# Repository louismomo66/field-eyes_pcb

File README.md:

# Field Eyes v2: full board schematic (KiCad 9)

Open `field_eyes_v2.kicad_pro` in KiCad 9. The whole circuit is **one flat schematic** (`field_eyes_v2.kicad_sch`): all 168 parts are on a single page, in four framed sections. The same page is in `field_eyes_v2.pdf`, and the parts list is in `field_eyes_v2_bom.csv`.

The design has 168 parts. KiCad's electrical rules check (ERC) reports 0 violations, and every net connects at least two pins.

**Status: schematic only.** There is no PCB layout yet. Nothing has been built or tested.

| Section (frame on the page) | Contents |
|---|---|
| Top of the page | Title, power tree, what changed from the old board, PCB layout notes |
| 1 Power (parts R1xx, C1xx...) | 6 V solar panel → CN3791 MPPT charger → 18650 cell with DW01A + FS8205 protection. XC6220 3.3 V regulator. AO3401A-switched +3V3_SW and +12V_SENS (MT3608 boost). Battery voltage, temperature and charge-status sensing. |
| 2 ESP32 (2xx) | ESP32-WROOM-32D. EN delay. Programming header **SV1** (the same 2 × 3 header and pin order as the old board: DTR, 3V3, TX, RX, RTS, GND) with auto-reset. OLED (**X3**) and DHT22 (**X4**) on 4-pin JST XH connectors with the old board's pinouts. 4 × M3 mounting holes. ESP32 pin map. |
| 3 Modem (3xx) | A7672S running straight from the cell, with 470 µF and the SIMCom capacitor set. PWRKEY and RESET drivers. UART level shifters. RI wake. Network LED. SIM holder with 22 Ω resistors and ESD. U.FL antenna with matching pads. Service header for modem firmware updates. |
| 4 Sensors and valve (4xx) | 2 × **MAX485ESA+T** RS485 (SMT100 on **X2**, 7-in-1 on **X1**) with automatic direction and SM712 protection. X1/X2 are 4-pin JST XH, pin 1 A, 2 B, 3 +12 V, 4 GND, as on the old board. A 78L05 (U405) makes the 5 V the MAX485 needs; dividers (3.3k/6.8k) bring its receive output down to 3.4 V for the ESP32. MX1508 driver for the latching valve (the chip from your mini-L298N module). |

The first version had four separate sheets behind placeholder boxes. Those files, and the board file as it was, are kept in `old_hierarchical/`; the circuit is identical (every net connects the same pins) and the board was relinked to the flat schematic.

`field_eyes.kicad_sym` holds custom symbols for the CN3791, FS8205, A7672S, SIM holder and SMF05C. The A7672S and SIM-holder footprints in `field_eyes.pretty` are copied from your current board, so they match what was already fabricated.

## Main decisions

- **Supply:** one Li-ion cell (VSYS 3.0–4.2 V).
  - The A7672S runs straight from it, as in SIMCom's reference design. That removes the MP2338 buck, the LM1117 and the D6/D7 diode drop.
  - Solar MPPT charging and cell protection are on the board.
  - Details and the battery-life estimate are in `../power_v2/README.md`. That earlier power-only project is now part of this one.
- **Everything that isn't needed is off by default.** The modem stays off until GPIO26 presses its power key. Sensors, RS485 chips, the DHT22 and the 12 V boost only get power while SENS_EN (GPIO13) is high.
- **Wake on message:** the modem's RI line goes to GPIO35 (an RTC pin), so the ESP32 can sleep and still react to a valve command immediately.
- **RS485:** the MAX485ESA+T from your old board. It needs 5 V, which this board no longer has, so U405 (78L05) makes +5V_SENS from the 12 V sensor rail; it is only powered while SENS_EN is on. The chip's receive output swings 0–5 V and the ESP32 pins are not 5 V tolerant, so each channel has a 3.3k/6.8k divider. Your auto-direction transistor trick is kept. The 120 Ω terminations are drawn but not fitted.
- **Valve:** the **MX1508**, the chip on your "mini L298N" driver board, is now on this board, using channel 1.
  - Same inputs as the module: IN1 = GPIO27 → INA1, IN2 = GPIO5 → INB1. H/L opens, L/H closes, both low = standby (< 0.1 µA). The firmware doesn't change.
  - The MX1508's motor supply must stay below 10 V (2–9.6 V for normal use), so it can't take the 12 V sensor rail.
  - Instead, a 78L09 charges a 4700 µF capacitor from the 12 V boost to about 8.7 V. It limits the current to about 0.1 A, so the battery protection can't trip. The capacitor then supplies the coil pulse, and a diode keeps it charged while the boost is off.
  - Solder jumper JP401 picks the valve supply: pads 1–2 (default) = 8.7 V for 9 V valves; pads 2–3 = the battery (3.0–4.2 V) for 3.6–6 V valves.
  - The chip's logic runs from +3V3, so the ESP32's 3.3 V signals are always within its input range. The second channel is unused (inputs tied low).
- **SIM, antenna and modem-service pads** follow the SIMCom A7672X hardware manual (figures 10, 13, 16, 22 and section 4.6).
- **GPS antenna:** kept, with the same circuit as the old board. U.FL connector **J304** takes an active antenna, fed from the modem's 2.8 V through R318 (0 Ω) and L301 (56 nH); C313 (33 pF) blocks the DC. The modem's built-in GNSS is linked to its UART3 by R320/R321 (1k), GNSS_PWRCTL goes to MK_IN_3 through R319 (10k), and 1V8_GNSS and GNSS_VBKP are powered. The firmware doesn't use GPS yet (the location is fixed). For a passive antenna, fit C313 only and leave R318/L301 off.

## Check these assumptions before ordering

1. **Valve voltage.** Check what supply your valve ran from on the module.
   - Up to about 9 V: leave JP401 on 1–2.
   - 3.6–6 V: move JP401 to 2–3.
   - A 12 V valve can't be driven by the MX1508 at its rated voltage, because the chip's limit is 10 V.
   - If the valve doesn't latch reliably, raise C403 to 6800–10000 µF.
   - The MX1508 channel is rated 1.5 A continuous and 2 A peak, so the coil should be at least about 5 Ω.
2. **Sensors at 12 V.** The Gemho 7-in-1 needs 9–18 V; the SMT100 accepts 4–24 V.
3. **GPS antenna type.** The bias circuit assumes an active antenna, like the old board. The GPS trace from J304 to the modem should be short and 50 Ω when you route it.

## Firmware changes this board needs (not made yet)

| What | Old board | New board |
|---|---|---|
| Modem power key | tied to GND (always on) | **GPIO26**: pulse HIGH 100–500 ms to switch on; switch off with `AT+CPOF` |
| Modem reset | GPIO19 (pulse direction wrong in the current firmware) | GPIO19: HIGH = reset (pulse 2.5 s), idle LOW |
| Sensor power | `SWITCH_PIN` 13 (placeholder) | GPIO13 = SENS_EN, unchanged. Also has to be on ≥ 1 s before every valve pulse, to top up the valve capacitor. |
| Battery voltage | GPIO34, old 78k/2k2 divider | GPIO34 × 2 |
| New inputs/outputs | — | GPIO35 RI wake; GPIO36 charging (low); GPIO39 cell temperature; GPIO14 stop charging |
| RS485 | MAX485 on 5 V | Same UART pins. Set the TX pins low or input before switching sensors off. |

## Next step: PCB layout (in KiCad)

1. In KiCad, open the PCB Editor, then **Tools → Update PCB from Schematic**. All footprints come in with their connections shown as ratsnest lines.
2. **Place parts**, following the layout notes at the top of the schematic page:
   - Keep the charger and boost switching loops tight.
   - Modem VBAT ≥ 2 mm wide, with C301–C306 at its pins.
   - 50 Ω RF trace from the modem to the U.FL.
   - ESP32 antenna over the board edge with no copper underneath.
   - Battery-temperature NTC (TH101) under the cell.
   - SM712s next to the JST sensor connectors X1/X2.
3. Route the board, pour ground on the bottom layer, then run DRC.
# field-eyes_pcb

## Connectors (as on the old board)

| Ref | What | Pins |
|---|---|---|
| SV1 | Programming, 2 × 3 header (MA03-2) | 1 DTR, 2 3V3, 3 TX0, 4 RX0, 5 RTS, 6 GND |
| X1 | 7-in-1 NPK sensor, JST XH 4-pin | 1 A, 2 B, 3 +12 V, 4 GND |
| X2 | SMT100, JST XH 4-pin | 1 A, 2 B, 3 +12 V, 4 GND |
| X3 | OLED, JST XH 4-pin | 1 3V3, 2 GND, 3 SDA, 4 SCL |
| X4 | DHT22, JST XH 4-pin | 1 not connected, 2 3V3 (switched), 3 DATA, 4 GND |

The solar input (J101) and the valve coil (J403) stay as 2-pin screw terminals because they carry more current. The board's old X5 (RGB LED / valve module) is gone: the valve driver is now on the board.

The board file was updated to match: the footprints are in `field_eyes.pretty`, which now includes the JST and SV1 footprints copied from your old board. The new parts were placed in free spots and are provisional. Files from before this change are in `backups/`.

## Board layout (follows the old design, sized for the enclosure)

**Enclosure:** DFRobot plastic project box, 5.83 × 3.70 × 2.36 in = about **148 × 94 × 60 mm** outside (the shop page gives only these overall figures; the interior is roughly 142 × 88 mm if the walls are about 3 mm).

The board is **118.3 × 68 mm** with 4 mm rounded corners. That leaves about 12 mm to the walls on the long sides and 10 mm on the short sides, which should keep it clear of the lid-screw posts in the corners. **Measure the inside of your box and its posts before ordering boards.** The 18650 holder (88 mm) lies on the back along the long side; the tallest part on the top is the 13 mm valve capacitor C403, so cell, board and parts stack to roughly 43 mm of the 55 mm inside height (also worth checking).

It is the old board's 100 × 60 mm layout, widened by 18 mm on the left and 8 mm at the bottom for the new circuits. Everything that was on the old board keeps its old arrangement:

- ESP32 left of centre with SV1 above it, and the GPS connector (J304) with its parts on the top edge
- the modem on the right, with the LTE antenna connector (J301) on the right edge
- the SIM tray (J302) on the **bottom edge** near the right corner, with its protection and resistors beside it
- the sensor connectors X2 (SMT100), X1 (7-in-1) and X4 (DHT22) along the bottom edge; X3 (OLED) beside the ESP32
- the modem control transistors in a row above the modem, the network LED and its transistor on the right edge, and the modem supply capacitors at the bottom right

New on the left: the solar charger, battery protection, 3.3 V regulator, 12 V boost and switches, the valve driver with its big capacitor, and the solar (J101) and valve (J403) terminals. The 18650 holder is on the back, with its temperature sensor.

All 168 parts are placed with no overlaps. There are no tracks yet. A smaller board also places (106 × 64 mm) but would be crowded and hard to route. `tools/place_like_old.py <board> <out> <extra width> <height>` redoes the placement at another size; the previous layouts are in `backups/`.

## No buttons

The RESET and BOOT buttons were removed. The board is reset and put in boot mode by the programming adapter on SV1 (RTS drives EN, DTR drives IO0, through the two-transistor auto-reset circuit), so flashing needs an adapter that brings out DTR and RTS on pins 1 and 5. Without a button there is no manual reset: switching the power off and on (or the adapter's RTS) does it.

## Even placement

After the first placement the parts were respread so that no area is crowded while others are empty: parts push each other apart with a light pull towards the parts they are wired to, and the parts that sit where they did on the old board (ESP32, modem, SIM tray, connectors) stay fixed. Parts keep out of the ESP32 antenna zone along the top edge and away from the battery holder's peg holes. Result: the unevenness of the part density across the free area is about halved, the wiring is shorter (signal nets about 8% less total length), and nothing overlaps. `tools/spread_parts.py` does it (export with `tools/export_placement.py`, apply with `tools/apply_positions.py`); the earlier placement is in `backups/field_eyes_v2.before_spreading.kicad_pcb`.

## GPS antenna corridor and RF lines

An antenna line needs a controlled 50 Ω track. On this 1.6 mm two-layer board that is a **microstrip about 3.0 mm wide** (calculated for FR4, εr 4.5, with the unbroken ground plane on the bottom layer under it), kept clear of other copper by about 1.5 mm each side, as short as possible, with ground vias along both sides, and tapered down to the 0.64 mm pad of the modem and the connector's centre pad. So the GPS part of the board is laid out around it:

- J304 (U.FL) sits on the top edge **just outside the ESP32 antenna zone**, with its centre pin facing the modem; the modem's GPS pad (P$90) is on the modem's top-left edge about 9 mm below it.
- The line runs from J304 straight down to the pad through **C313 (33 pF, in line)**: about 12 mm in all.
- L301 and R318 (the antenna bias) sit off to the side, away from the line; the bias is DC and can take any route.
- A **clear corridor** of 13 × 10 mm around the line holds no other part, and the spreading tool keeps it that way. The area under it on the bottom layer is free for the ground plane.

Route `/GPS_ANT`, `/GPS_SIG` (and the LTE nets `/RF_ANT`, `/ANT_FEED`) **by hand**, with a 3.0 mm track, not with the autorouter. `tools/dsn_without.py` makes `routing/field_eyes_v2_autoroute.dsn` without those nets and without ground (ground comes from the pours). The LTE line (modem right edge to J301, about 8 mm) needs the same width and clearance; its parts are placed along the straight line to J301, but it was not given a protected corridor of its own.

## Antenna lines are routed

Both antenna lines are routed on the top layer (`tools/route_antennas.py`) and pass KiCad's design-rule check with no clearance, short or keep-out errors on these nets:

- **GPS:** modem pad -> 3.0 mm track (50 ohm) up the corridor -> C313 -> J304, about 12 mm. The width steps down 0.64 / 1.4 / 2.2 / 3.0 mm leaving the modem pad (round track ends need the steps spaced out) and narrows to 0.6 mm at C313 and 1.0 mm at the connector. The bias branch (thin, DC) runs west below the ESP32 antenna zone to L301 and R318.
- **LTE:** modem pad -> R317 -> J301, about 8 mm. Only 2.2 mm wide (about 60 ohm) near R317, because there is not room for 3 mm next to the resistor; 1.0 mm between R317 and the connector. J301 was turned so that its centre pin faces the modem; C311 and C312 (unfitted tuning capacitors) hang off the line with vias to ground.
- U.FL ground pads and the matching-capacitor ground pads have vias to the **bottom ground plane** (a full-board GND fill on the bottom layer), which is the 50 ohm reference for both lines.
- **Full routing:** every signal and power net (111 nets, 253 connections) is routed on the two layers with `tools/route_board.sh`, which uses a purpose-built grid router (`tools/router.cpp`, 0.1 mm grid, negotiated congestion, 0.2 mm clearance, 0.25 mm signal tracks, 0.35–0.5 mm power tracks, 0.6/0.3 mm vias). Freerouting was dropped because it never finished on this board. Ground is not routed as tracks: the two planes carry it, a few ground pads get a short stub to a via, and `tools/stitch_fragments.py` / `tools/gnd_groups.py` / `tools/dedupe_vias.py` join the pieces of the planes that the signal tracks cut apart. The programming header SV1 was moved 6.4 mm down (and R205–R207 2 mm down) so that it is outside the ESP32 antenna keep-out. The widest power net, the modem supply `/MODEM_VBAT`, ended up 0.5 mm wide (0.8 mm did not fit between the modem pads). Result: DRC has no clearance, short or connection errors and nothing left unrouted; only silkscreen/courtyard notices remain.
- **Ground planes (SIM7600/A7672S hardware guide, section 4.2):** a full-board GND pour on **both** layers (`GND_TOP`, `GND_BOTTOM`), tied together by 29 stitching vias along the board edge and beside the RF lines. The bottom plane is the unbroken 50 ohm reference; the top pour is cut back 1 mm from each side of the two antenna lines (rule areas `KO_RF_LTE`, `KO_RF_GPS`) so that it does not pull the impedance down. Neither pour enters the ESP32's antenna keep-out (x 30.2–78.2, y 0–9.1 mm). The LTE line follows the guide's matching-network layout: connector close to the module, 0 Ω series R317 with the two unfitted shunt capacitor pads C311/C312 (the guide's R1/R2 + C1/C2); the optional TVS is not fitted. Active-GPS-antenna bias follows guide Figure 37 (33 pF DC block, 56 nH, supply from the modem's 2.8 V). Run `tools/route_antennas.py` to rebuild them.

Everything else is still unrouted. The remaining design-rule notices are not about the antennas: SV1's pins sit inside the ESP32 antenna keep-out zone (as it did on your old board; move it if the Wi-Fi range matters), and the ESP32's thermal-pad vias have small drills (from the stock footprint). `routing/field_eyes_v2_autoroute.dsn` leaves out ground and the antenna nets.

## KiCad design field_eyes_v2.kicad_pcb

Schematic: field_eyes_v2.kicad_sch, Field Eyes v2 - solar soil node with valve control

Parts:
BT101: 18650 Li-ion 3000mAh; BatteryHolder_Keystone_1042_1x18650_2pegs
C101, C114: 22uF 25V; C_1206_3216Metric
C102, C103, C106, C107, C203, C310, C401, C402, C404, C406, C407: 100nF; C_0603_1608Metric
C104: 220nF; C_0603_1608Metric
C105, C113: 22uF 10V; C_0805_2012Metric
C108, C111, C202: 10uF; C_0805_2012Metric
C109, C110: 47nF; C_0603_1608Metric
C112, C201, C309, C409: 1uF; C_0603_1608Metric
C204: 47uF 6.3V; C_1206_3216Metric
C301: 470uF 6.3V low-ESR; CP_EIA-7343-31_Kemet-D
C302: 22uF; C_0805_2012Metric
C303: 1uF; C_0402_1005Metric
C304: 100nF; C_0402_1005Metric
C305, C313: 33pF; C_0402_1005Metric
C306: 10pF; C_0402_1005Metric
C307, C308: 1nF; C_0603_1608Metric
C311, C312: NM; C_0402_1005Metric; not fitted
C403: 4700uF 16V; CP_Radial_D12.5mm_P5.00mm
C405, C408: 330nF 25V; C_0603_1608Metric
D101, D102, D103, D403: SS14; D_SMA
D301: ESD5Z5.0T1G; D_SOD-523
D302: RED 0603; LED_0603_1608Metric
D401, D402: SM712; SOT-23
FB301: BLM21PG300SN1D; L_0805_2012Metric
H201, H202, H203, H204: M3; MountingHole_3.2mm_M3
J101: SOLAR 6V; TerminalBlock_Phoenix_PT-1,5-2-3.5-H_1x02_P3.50mm_Horizontal
J301: U.FL LTE; U.FL_Hirose_U.FL-R-SMT-1_Vertical
J302: SIM holder (TE 2199337-5); TE_2199337-5
J303: MODEM USB (DNP); PinHeader_1x06_P1.27mm_Vertical; not fitted
J304: U.FL GPS; U.FL_Hirose_U.FL-R-SMT-1_Vertical
J403: VALVE coil; TerminalBlock_Phoenix_PT-1,5-2-3.5-H_1x02_P3.50mm_Horizontal
JP401: VALVE SUPPLY; SolderJumper-3_P1.3mm_Bridged12_RoundedPad1.0x1.5mm
L101, L102: 22uH 2A shielded; L_Bourns_SRN6045TA
L301: 56nH; L_0805_2012Metric
Q101, Q102, Q105, Q107: AO3401A; SOT-23
Q103, Q106, Q108: 2N7002; SOT-23
Q104: FS8205; SOT-23-6
Q201, Q202, Q301, Q302, Q303, Q304, Q305, Q306, Q401, Q402: MMBT3904; SOT-23
R101, R115, R120, R201, R202, R203, R204, R207, R310, R319, R402, R412: 10k; R_0603_1608Metric
R103: 0R12 1% 0.25W; R_1206_3216Metric
R104: 120R; R_0603_1608Metric
R105: 348k 1%; R_0603_1608Metric
R106: 100k 1%; R_0603_1608Metric
R107, R108, R114, R116, R117, R421, R422: 100k; R_0603_1608Metric
R109: 100R; R_0603_1608Metric
R110, R320, R321: 1k; R_0603_1608Metric
R111, R112: 470k 1%; R_0603_1608Metric
R113, R119: 10k 1%; R_0603_1608Metric
R118: 191k 1%; R_0603_1608Metric
R205, R206, R301, R303, R305, R306, R307, R308, R309, R311, R401, R403, R404, R411, R413, R414: 4.7k; R_0603_1608Metric
R302, R304, R312: 47k; R_0603_1608Metric
R313: 2.2k; R_0603_1608Metric
R314, R315, R316: 22R; R_0603_1608Metric
R317: 0R; R_0402_1005Metric
R318: 0R; R_0603_1608Metric
R405, R406, R415, R416: 10R; R_0603_1608Metric
R407, R417: 120R; R_0603_1608Metric; not fitted
R423, R425: 3.3k; R_0603_1608Metric
R424, R426: 6.8k; R_0603_1608Metric
SV1: PROG (as old SV1); MA03-2
TH101: 10k B3950 (under cell); R_0603_1608Metric
TP301: STATUS; TestPoint_Pad_D1.5mm
U101: CN3791; SSOP-10_3.9x4.9mm_P1.00mm
U102: DW01A; SOT-23-6
U103: XC6220B331MR; SOT-23-5
U104: MT3608; SOT-23-6
U201: ESP32-WROOM-32D
U301: A7672S
U302: SMF05C; SOT-363_SC-70-6
U401, U402: MAX485ESA+T; SOIC-8_3.9x4.9mm_P1.27mm
U403: MX1508; SOIC-16_3.9x9.9mm_P1.27mm
U404: L78L09; SOT-89-3
U405: L78L05; SOT-89-3
X1: 7-in-1 NPK (A B 12V GND); JST_XH_04_LongPad
X2: SMT100 (A B 12V GND); JST_XH_04_LongPad
X3: OLED (3V3 GND SDA SCL); JST_XH_04_LongPad
X4: DHT22 (NC 3V3 DATA GND); JST_XH_04_LongPad

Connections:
+3V3: C110.1, C111.1, C202.1, C203.1, C204.1, C407.1, Q107.2 (S), R107.2, R117.1, R201.1, R202.1, R205.1, R206.1, R306.1, R310.1, SV1.2, U103.5 (VOUT), U201.2 (VDD), U301.P$116 (GNSS_VBKP), U403.1 (VCC1), U403.5 (VCC2), X3.1
+3V3_SW: C112.1, Q107.3 (D), R113.1, R207.1, X4.2
+5V_SENS: C401.1, C402.1, C409.1, R402.1, R403.1, R412.1, R413.1, U401.8 (VCC), U402.8 (VCC), U405.1 (OUT)
+12V_SENS: C114.1, C405.1, C408.1, D103.1 (K), R118.1, U404.3 (IN), U405.3 (IN), X1.3, X2.3
/ANT_FEED: C312.1, J301.1 (In), R317.2
/BATN: BT101.2 (-), C106.2, Q104.1 (S1), U102.6 (GND)
/BST_FB: R118.2, R119.1, U104.3 (FB)
/BST_SW: D103.2 (A), L102.2, U104.1 (SW)
/CHG_COM: R104.1, U101.5 (COM)
/CHG_COMC: C104.1, R104.2
/CHG_CSP: L101.2, R103.1, U101.8 (CSP)
/CHG_D: D101.2 (A), Q102.3 (D)
/CHG_GATE: Q102.1 (G), U101.10 (DRV)
/CHG_SW: D101.1 (K), D102.1 (K), L101.1
/CHG_VG: C103.1, U101.1 (VG)
/DHT_DATA: R207.2, U201.26 (IO4), X4.3
/DW_CS: R110.1, U102.2 (CS)
/DW_OC: Q104.4 (G2), U102.3 (OC)
/DW_OD: Q104.6 (G1), U102.1 (OD)
/DW_VCC: C106.1, R109.2, U102.5 (VCC)
/ESP_EN: C201.1, Q201.3 (C), R201.2, U201.3 (EN)
/ESP_IO0: Q202.3 (C), R202.2, U201.25 (IO0)
/GNSS_PWRCTL: R319.1, U301.P$98 (GNSS_PWRCTL)
/GNSS_RXD: R320.1, U301.P$96 (GNSS_RXD)
/GNSS_TXD: R321.1, U301.P$95 (GNSS_TXD)
/GPS_ANT: C313.1, U301.P$90 (GPS_ANT)
/GPS_BIAS: L301.2, R318.1
/GPS_SIG: C313.2, J304.1 (In), L301.1
/GSM_RX: Q304.3 (C), R308.2, U301.P$10 (U1_RXD)
/GSM_TX: Q303.2 (E), U301.P$9 (U1_TXD)
/I2C_SCL: R205.2, U201.36 (IO22), X3.4
/I2C_SDA: R206.2, U201.33 (IO21), X3.3
/MDM_LOG_TX: J303.6, U301.P$23 (UART_LOG_TX)
/MDM_STATUS: TP301.1, U301.P$66 (STATUS)
/MDM_USB_BOOT: J303.5, U301.P$6 (USB_BOOT)
/MDM_USB_DM: J303.3, U301.P$28 (USB_DM)
/MDM_USB_DP: J303.4, U301.P$27 (USB_DP)
/MDM_VBUS: J303.2, U301.P$24 (VBUS)
/MK_IN_3: R319.2, U301.P$20 (MK_IN_3)
/MODEM_PWRKEY: Q301.3 (C), U301.P$1 (PWRKEY)
/MODEM_RESET: Q302.3 (C), U301.P$16 (RESET)
/MODEM_RI: Q305.2 (E), U301.P$4 (U1_RI)
/MODEM_VBAT: C301.1, C302.1, C303.1, C304.1, C305.1, C306.1, D301.1 (K), FB301.2, R313.1, U301.P$55 (VBAT), U301.P$56 (VBAT), U301.P$57 (VBAT)
/MPPT: Q103.3 (D), R105.2, R106.1, U101.6 (MPPT)
/MX_VDD: C404.1, JP401.2 (C), U403.4 (VDD1), U403.8 (VDD2)
/NETLIGHT: R311.1, U301.P$52 (NETLIGHT)
/NL_A: D302.2 (A), R313.2
/NL_B: Q306.1 (B), R311.2, R312.1
/NL_K: D302.1 (K), Q306.3 (C)
/PK_B: Q301.1 (B), R301.2, R302.1
/PROG_DTR: Q202.2 (E), R203.1, SV1.1
/PROG_RTS: Q201.2 (E), R204.1, SV1.5
/PROT_D: Q104.2 (D12), Q104.5 (D12)
/Q1G: Q101.1 (G), R101.1
/Q5_G: C109.2, Q105.1 (G), R114.2, R115.1
/Q5_GD: Q106.3 (D), R115.2
/Q7_G: C110.2, Q107.1 (G), R117.2, R120.1
/Q7_GD: Q108.3 (D), R120.2
/Q201B: Q201.1 (B), R203.2
/Q202B: Q202.1 (B), R204.2
/RF_ANT: C311.1, R317.1, U301.P$60 (RF_ANT)
/RIQ_B: Q305.1 (B), R309.2
/RS1_A: D401.1 (A1), R405.2, R407.1, X2.1
/RS1_AI: R403.2, R405.1, U401.6 (A)
/RS1_B: D401.2 (A2), R406.2, R407.2, X2.2
/RS1_BI: R404.1, R406.1, U401.7 (B)
/RS1_EN: Q401.3 (C), R402.2, U401.2 (~RE), U401.3 (DE)
/RS1_QB: Q401.1 (B), R401.2
/RS1_RO: R423.1, U401.1 (RO)
/RS2_A: D402.1 (A1), R415.2, R417.1, X1.1
/RS2_AI: R413.2, R415.1, U402.6 (A)
/RS2_B: D402.2 (A2), R416.2, R417.2, X1.2
/RS2_BI: R414.1, R416.1, U402.7 (B)
/RS2_EN: Q402.3 (C), R412.2, U402.2 (~RE), U402.3 (DE)
/RS2_QB: Q402.1 (B), R411.2
/RS2_RO: R425.1, U402.1 (RO)
/RST_B: Q302.1 (B), R303.2, R304.1
/RXQ_B: C308.2, Q304.1 (B), R307.2
/SENS_VIN: C113.1, L102.1, Q105.3 (D), U104.4 (EN), U104.5 (IN)
/SIM_CLK: J302.C3 (CLK), R315.2, U302.4 (IO3)
/SIM_CLK_M: R315.1, U301.P$32 (SIM_CLK)
/SIM_DATA_M: R314.1, U301.P$31 (SIM_DATA)
/SIM_IO: J302.C7 (I/O), R314.2, U302.3 (IO2)
/SIM_RST: J302.C2 (RST), R316.2, U302.5 (IO4)
/SIM_RST_M: R316.1, U301.P$33 (SIM_RST)
/SIM_VDD: C310.1, J302.C1 (VCC), U301.P$30 (SIM_VDD), U302.1 (IO1)
/SOLAR_P: C101.1, C102.1, C103.2, Q101.2 (S), Q102.2 (S), R105.1, U101.9 (VCC)
/SOLAR_RAW: J101.1, Q101.3 (D)
/TXQ_B: C307.2, Q303.1 (B), R305.2
/U0_RXD: SV1.4, U201.34 (RXD0/IO3)
/U0_TXD: SV1.3, U201.35 (TXD0/IO1)
/U3_RXD: R320.2, U301.P$49 (U3_RXD)
/U3_TXD: R321.2, U301.P$50 (U3_TXD)
/VALVE_9V: C406.1, D403.2 (A), U404.1 (OUT)
/VALVE_A: J403.1, U403.16 (OUTA1)
/VALVE_B: J403.2, U403.13 (OUTB1)
/VALVE_RES: C403.1, D403.1 (K), JP401.1 (A)
/VDD_1V8: C307.1, C308.1, C309.1, R305.1, R307.1, R308.1, R309.1, U301.P$15 (VDD_1V8), U301.P$97 (1V8_GNSS)
/VDD_2V8: R318.2, U301.P$99 (VDD_2V8)
BAT_TEMP: R113.2, TH101.1, U201.5 (SENSOR_VN)
BAT_V: C107.1, R111.2, R112.1, U201.6 (IO34)
CHG_INHIBIT: Q103.1 (G), R108.1, U201.13 (IO14)
CHG_STAT: R107.1, U101.3 (~CHRG), U201.4 (SENSOR_VP)
GND: C101.2, C102.2, C104.2, C105.2, C107.2, C108.2, C111.2, C112.2, C113.2, C114.2, C201.2, C202.2, C203.2, C204.2, C301.2, C302.2, C303.2, C304.2, C305.2, C306.2, C309.2, C310.2, C311.2, C312.2, C401.2, C402.2, C403.2, C404.2, C405.2, C406.2, C407.2, C408.2, C409.2, D102.2 (A), D301.2 (A), D401.3 (common), D402.3 (common), J101.2, J301.2 (Ext), J302.C5 (GND), J302.G1 (GND), J302.G2 (GND), J302.G3 (GND), J302.G4 (GND), J303.1, J304.2 (Ext), Q103.2 (S), Q104.3 (S2), Q106.2 (S), Q108.2 (S), Q301.2 (E), Q302.2 (E), Q306.2 (E), Q401.2 (E), Q402.2 (E), R101.2, R106.2, R108.2, R110.2, R112.2, R116.2, R119.2, R302.2, R304.2, R312.2, R404.2, R414.2, R421.2, R422.2, R424.2, R426.2, SV1.6, TH101.2, U101.2 (GND), U101.4 (~DONE), U103.2 (GND), U104.2 (GND), U201.1 (GND), U201.15 (GND), U201.38 (GND), U201.39 (GND), U301.P$2 (GND), U301.P$17 (GND), U301.P$18 (GND), U301.P$29 (GND), U301.P$39 (GND), U301.P$45 (GND), U301.P$46 (GND), U301.P$54 (GND), U301.P$58 (GND), U301.P$59 (GND), U301.P$61 (GND), U301.P$62 (GND), U301.P$63 (GND), U301.P$64 (GND), U301.P$65 (GND), U301.P$69 (GND), U301.P$70 (GND), U301.P$71 (GND), U301.P$72 (GND), U301.P$73 (GND), U301.P$74 (GND), U301.P$75 (GND), U301.P$76 (GND), U301.P$77 (GND), U301.P$78 (GND), U301.P$79 (GND), U301.P$80 (GND), U301.P$81 (GND), U301.P$82 (GND), U301.P$83 (GND), U301.P$84 (GND), U301.P$85 (GND), U301.P$86 (GND), U301.P$87 (GND), U301.P$88 (GND), U301.P$89 (GND), U301.P$91 (GND), U301.P$92 (GND), U301.P$94 (GND), U302.2 (GND), U401.5 (GND), U402.5 (GND), U403.6 (INA2), U403.7 (INB2), U403.10 (AGND2), U403.11 (PGND2), U403.14 (AGND1), U403.15 (PGND1), U404.2 (GND), U405.2 (GND), X1.4, X2.4, X3.2, X4.4
MCU_RX: Q303.3 (C), R306.2, U201.28 (IO17)
MCU_TX: Q304.2 (E), U201.27 (IO16)
MODEM_RST_CTL: R303.1, U201.31 (IO19)
NPK_RX: R425.2, R426.1, U201.8 (IO32)
NPK_TX: R411.1, U201.9 (IO33), U402.4 (DI)
PWRKEY_CTL: R301.1, U201.11 (IO26)
RI_WAKE: Q305.3 (C), R310.2, U201.7 (IO35)
SENS_EN: Q106.1 (G), Q108.1 (G), R116.1, U201.16 (IO13)
SMT_RX: R423.2, R424.1, U201.10 (IO25)
SMT_TX: R401.1, U201.37 (IO23), U401.4 (DI)
VALVE_IN1: R421.1, U201.12 (IO27), U403.2 (INA1)
VALVE_IN2: R422.1, U201.29 (IO5), U403.3 (INB1)
VSYS: BT101.1 (+), C105.1, C108.1, C109.1, FB301.1, JP401.3 (B), Q105.2 (S), R103.2, R109.1, R111.1, R114.1, U101.7 (BAT), U103.1 (VIN), U103.3 (CE)

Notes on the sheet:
A. SOLAR INPUT + MPPT CHARGER (CN3791, 1 cell, 4.2 V)
Panel: 6 V nominal, 1-2 W (Voc <= 8 V). Q101 = reverse-polarity protection (on when the panel is the right way round). Charge current = 120 mV / R103 = 1.0 A max (the panel limits it further). MPPT holds the panel at 1.205 V x (1 + R105/R106) = 5.40 V, a little under Vmp so it still tracks when the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
B. BATTERY (1 x 18650 Li-ion) + PROTECTION + SENSING
DW01A + FS8205 cut the cell off below 2.4 V, above 4.3 V, on over-current (~3 A) and short circuit. Board ground is the protected P- side; BATN is the cell minus. VSYS = cell + (3.0-4.2 V) feeds the modem directly (SIMCom reference design: no regulator, no diodes), the 3.3 V LDO and the 12 V boost.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
C. 3.3 V REGULATOR, SWITCHED SENSOR POWER (AO3401A) AND 12 V SENSOR / VALVE BOOST
U103 XC6220: 1 A, 8 uA quiescent, ~0.1 V dropout -> the ESP32 still gets ~3.2 V from a 3.3 V cell. SENS_EN (GPIO13) high turns on BOTH Q105 (cell -> boost) and Q107 (+3V3 -> RS485/DHT22/NTC). Off by default: R116 holds SENS_EN low while the ESP32 boots or sleeps. Each AO3401A gate is pulled to its 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
Power flags (ERC only)
1 POWER: SOLAR CHARGER, BATTERY, 3.3 V AND SWITCHED RAILS
ESP32-WROOM-32D
EN: 10k + 1 uF delay (Espressif reference) so the chip starts only after 3.3 V is stable. Q201/Q202: the usual two-transistor auto-reset, so esptool can reset and enter the bootloader through DTR/RTS of a USB-serial adapter (same pin order as the old SV1 header). Strapping pins IO0/IO2/IO12/IO15 ar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
PROGRAMMING (USB-serial adapter, 3.3 V logic)
OLED (SSD1306, I2C 0x3C) DHT22 (powered only while reading)
ESP32 PIN MAP IO13 SENS_EN out high = 12 V sensors/valve boost + RS485 + DHT22 + NTC powered IO26 PWRKEY_CTL out high pulse 100-500 ms = press the modem power key IO19 MODEM_RST_CTL out high = hold the modem in reset (pulse 2.5 s) IO16/IO17 modem UART TX/RX (115200, through MMBT3904 level shifters)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
2 ESP32, PROGRAMMING, DISPLAY, DHT22
A7672S LTE CAT-1 MODEM
Powered straight from the cell (VSYS) through FB301: SIMCom reference for a 1-cell Li-ion supply. 470 uF low-ESR plus 22u/1u/100n/33p/10p near the VBAT pins (route VBAT >= 2 mm wide). D301 clamps surges. PWRKEY and RESET are driven by MMBT3904s (SIMCom figures 10 and 13: 4.7k base, 47k pull-down), 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
VBAT
POWER KEY
RESET
UART modem -> ESP32
UART ESP32 -> modem
RI wake
NETWORK LED
SIM CARD (SIMCom figure 22: 22 R series, 100 nF, ESD array next to the holder)
LTE ANTENNA (SIMCom 4.6: 0 R + two unfitted shunt caps for matching; keep the RF trace 50 ohm and short)
MODEM SERVICE PADS (SIMCom: reserve USB, USB_BOOT and LOG test points for firmware upgrades)
3 A7672S LTE MODEM, SIM, ANTENNA
RS485 SOIL SENSORS (two buses: the SMT100 is 8E1, the 7-in-1 8N1)
MAX485ESA+T (the chip on the old board) on +5V_SENS, made by U405 (78L05) from the 12 V sensor rail, so it only has power while SENS_EN is on. RO swings 0-5 V: the 3.3k + 6.8k divider gives the ESP32 3.4 V (its pins are not 5 V tolerant). Direction is automatic: TX idle-high turns the MMBT3904 on a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
SMT100
7-in-1 NPK
LATCHING VALVE DRIVER (MX1508 - the chip on the "mini L298N" module)
U403 = MX1508, channel 1: IN1 (GPIO27) high = OUTA high (open); IN2 (GPIO5) high = OUTB high (close); both low = standby < 0.1 uA. Same logic as the module, so the firmware does not change. Its motor supply must stay below 10 V, so the 12 V boost charges C403 through a 78L09 (current-limited, ~0.1 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
4 SOIL SENSORS (RS485) AND VALVE DRIVER
FIELD EYES v2 - solar soil-monitoring node with latching valve control
POWER TREE 6 V panel (1-2 W) -> CN3791 MPPT charger -> 18650 cell (DW01A/FS8205 protection) = VSYS 3.0-4.2 V VSYS -> A7672S VBAT directly (2 A bursts) VSYS -> XC6220 -> +3V3 (ESP32, always on) +3V3 -> AO3401A (SENS_EN) -> +3V3_SW (RS485, DHT22, NTC) VSYS -> AO3401A (SENS_EN) -> MT3608 -> +12V_SENS 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
GPS ANTENNA (active antenna, as on the old board): the modem's 2.8 V feeds the antenna through R318 + L301 (56 nH); C313 blocks the DC. The built-in GNSS UART is linked to UART3 through R320/R321 and GNSS_PWRCTL goes to MK_IN_3 through R319 (SIMCom 3.11). 1V8_GNSS and GNSS_VBKP are powered. For a p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

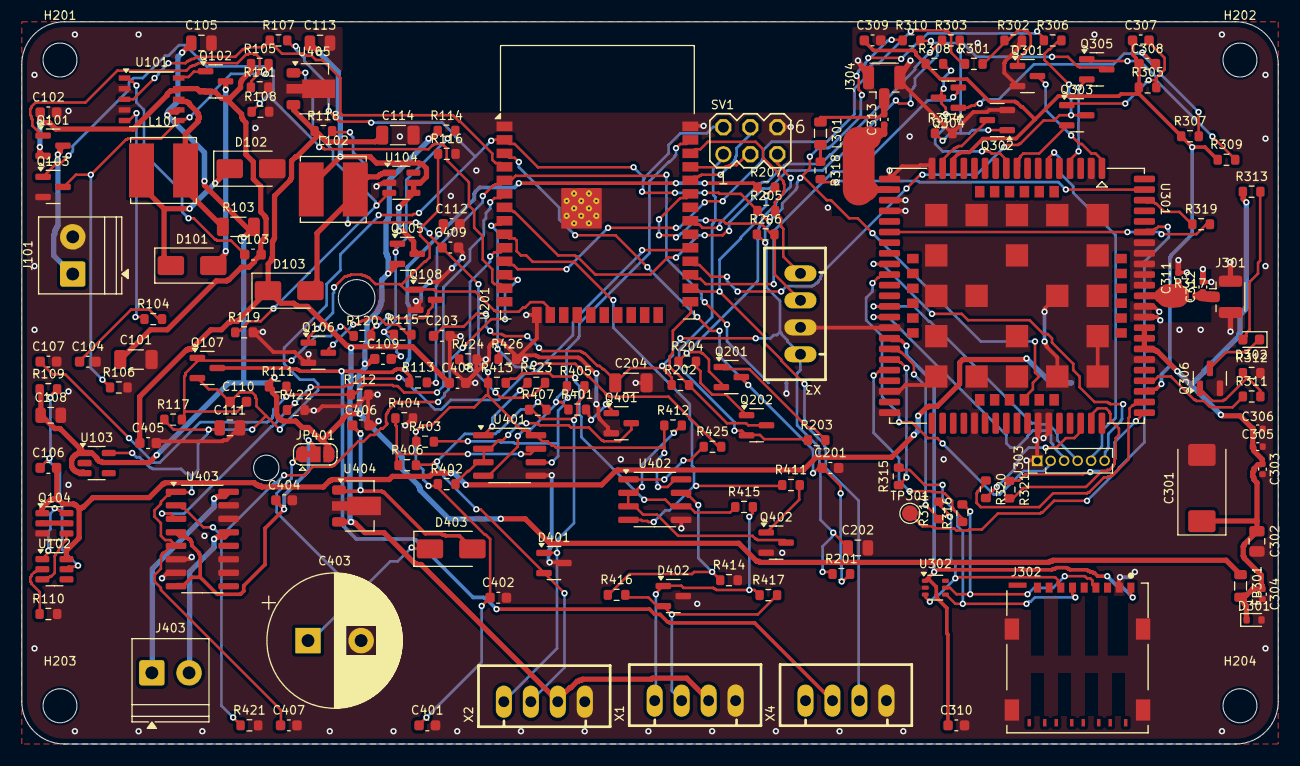
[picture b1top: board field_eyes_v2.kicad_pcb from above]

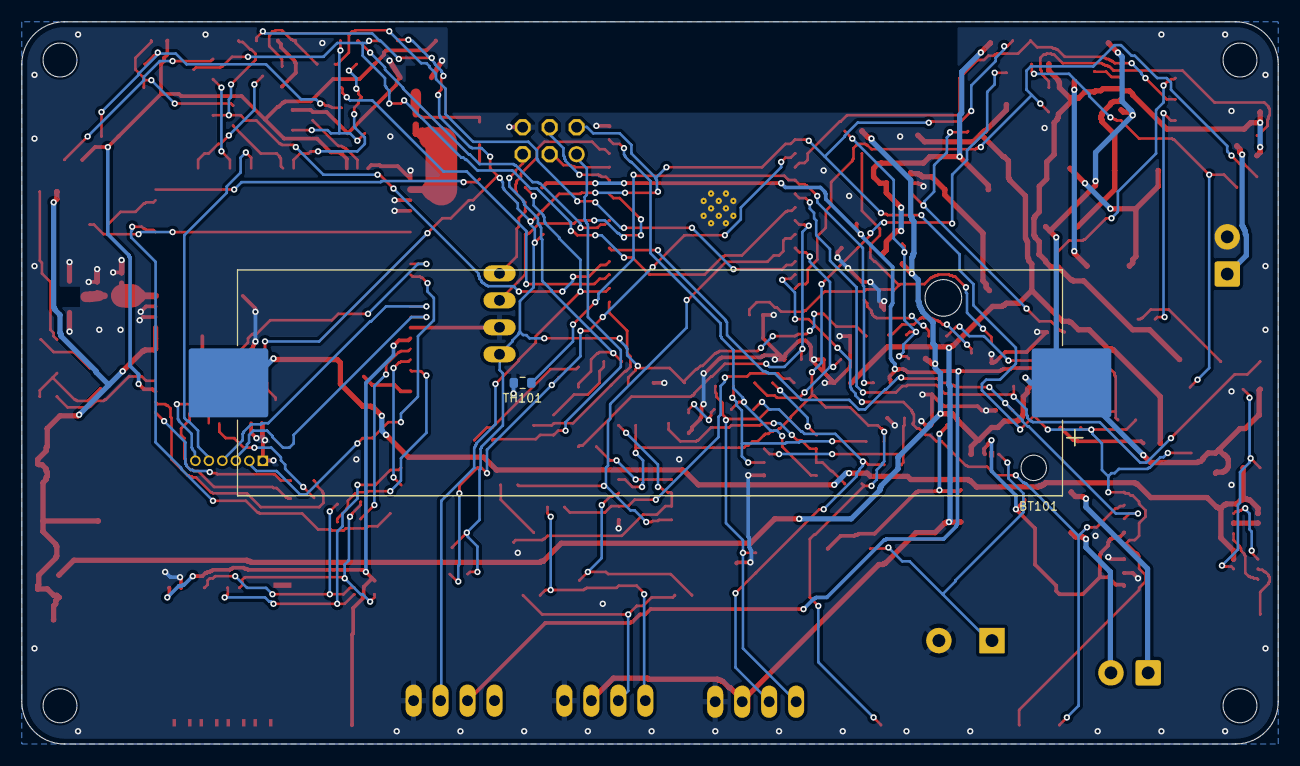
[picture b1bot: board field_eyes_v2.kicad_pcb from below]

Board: 2 copper layers, 118.3 x 68.0 mm, 168 parts (2 on the bottom side), 117 nets.

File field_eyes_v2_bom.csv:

"Refs","Value","Footprint","Qty","DNP"
"BT101","18650 Li-ion 3000mAh","field_eyes:BatteryHolder_Keystone_1042_1x18650_2pegs","1",""
"C101,C114","22uF 25V","Capacitor_SMD:C_1206_3216Metric","2",""
"C102,C103,C106,C107,C203,C310,C401,C402,C404,C406,C407","100nF","Capacitor_SMD:C_0603_1608Metric","11",""
"C104","220nF","Capacitor_SMD:C_0603_1608Metric","1",""
"C105,C113","22uF 10V","Capacitor_SMD:C_0805_2012Metric","2",""
"C108,C111,C202","10uF","Capacitor_SMD:C_0805_2012Metric","3",""
"C109,C110","47nF","Capacitor_SMD:C_0603_1608Metric","2",""
"C112,C201,C309,C409","1uF","Capacitor_SMD:C_0603_1608Metric","4",""
"C204","47uF 6.3V","Capacitor_SMD:C_1206_3216Metric","1",""
"C301","470uF 6.3V low-ESR","Capacitor_Tantalum_SMD:CP_EIA-7343-31_Kemet-D","1",""
"C302","22uF","Capacitor_SMD:C_0805_2012Metric","1",""
"C303","1uF","Capacitor_SMD:C_0402_1005Metric","1",""
"C304","100nF","Capacitor_SMD:C_0402_1005Metric","1",""
"C305,C313","33pF","Capacitor_SMD:C_0402_1005Metric","2",""
"C306","10pF","Capacitor_SMD:C_0402_1005Metric","1",""
"C307,C308","1nF","Capacitor_SMD:C_0603_1608Metric","2",""
"C311,C312","NM","Capacitor_SMD:C_0402_1005Metric","2","DNP"
"C403","4700uF 16V","Capacitor_THT:CP_Radial_D12.5mm_P5.00mm","1",""
"C405,C408","330nF 25V","Capacitor_SMD:C_0603_1608Metric","2",""
"D101,D102,D103,D403","SS14","Diode_SMD:D_SMA","4",""
"D301","ESD5Z5.0T1G","Diode_SMD:D_SOD-523","1",""
"D302","RED 0603","LED_SMD:LED_0603_1608Metric","1",""
"D401,D402","SM712","Package_TO_SOT_SMD:SOT-23","2",""
"FB301","BLM21PG300SN1D","Inductor_SMD:L_0805_2012Metric","1",""
"H201,H202,H203,H204","M3","MountingHole:MountingHole_3.2mm_M3","4",""
"J101","SOLAR 6V","TerminalBlock_Phoenix:TerminalBlock_Phoenix_PT-1,5-2-3.5-H_1x02_P3.50mm_Horizontal","1",""
"J301","U.FL LTE","Connector_Coaxial:U.FL_Hirose_U.FL-R-SMT-1_Vertical","1",""
"J302","SIM holder (TE 2199337-5)","field_eyes:TE_2199337-5","1",""
"J303","MODEM USB (DNP)","Connector_PinHeader_1.27mm:PinHeader_1x06_P1.27mm_Vertical","1","DNP"
"J304","U.FL GPS","Connector_Coaxial:U.FL_Hirose_U.FL-R-SMT-1_Vertical","1",""
"J403","VALVE coil","TerminalBlock_Phoenix:TerminalBlock_Phoenix_PT-1,5-2-3.5-H_1x02_P3.50mm_Horizontal","1",""
"JP401","VALVE SUPPLY","Jumper:SolderJumper-3_P1.3mm_Bridged12_RoundedPad1.0x1.5mm","1",""
"L101,L102","22uH 2A shielded","Inductor_SMD:L_Bourns_SRN6045TA","2",""
"L301","56nH","Inductor_SMD:L_0805_2012Metric","1",""
"Q101,Q102,Q105,Q107","AO3401A","Package_TO_SOT_SMD:SOT-23","4",""
"Q103,Q106,Q108","2N7002","Package_TO_SOT_SMD:SOT-23","3",""
"Q104","FS8205","Package_TO_SOT_SMD:SOT-23-6","1",""
"Q201,Q202,Q301,Q302,Q303,Q304,Q305,Q306,Q401,Q402","MMBT3904","Package_TO_SOT_SMD:SOT-23","10",""
"R101,R115,R120,R201,R202,R203,R204,R207,R310,R319,R402,R412","10k","Resistor_SMD:R_0603_1608Metric","12",""
"R103","0R12 1% 0.25W","Resistor_SMD:R_1206_3216Metric","1",""
"R104","120R","Resistor_SMD:R_0603_1608Metric","1",""
"R105","348k 1%","Resistor_SMD:R_0603_1608Metric","1",""
"R106","100k 1%","Resistor_SMD:R_0603_1608Metric","1",""
"R107,R108,R114,R116,R117,R421,R422","100k","Resistor_SMD:R_0603_1608Metric","7",""
"R109","100R","Resistor_SMD:R_0603_1608Metric","1",""
"R110,R320,R321","1k","Resistor_SMD:R_0603_1608Metric","3",""
"R111,R112","470k 1%","Resistor_SMD:R_0603_1608Metric","2",""
"R113,R119","10k 1%","Resistor_SMD:R_0603_1608Metric","2",""
"R118","191k 1%","Resistor_SMD:R_0603_1608Metric","1",""
"R205,R206,R301,R303,R305,R306,R307,R308,R309,R311,R401,R403,R404,R411,R413,R414","4.7k","Resistor_SMD:R_0603_1608Metric","16",""
"R302,R304,R312","47k","Resistor_SMD:R_0603_1608Metric","3",""
"R313","2.2k","Resistor_SMD:R_0603_1608Metric","1",""
"R314,R315,R316","22R","Resistor_SMD:R_0603_1608Metric","3",""
"R317","0R","Resistor_SMD:R_0402_1005Metric","1",""
"R318","0R","Resistor_SMD:R_0603_1608Metric","1",""
"R405,R406,R415,R416","10R","Resistor_SMD:R_0603_1608Metric","4",""
"R407,R417","120R","Resistor_SMD:R_0603_1608Metric","2","DNP"
"R423,R425","3.3k","Resistor_SMD:R_0603_1608Metric","2",""
"R424,R426","6.8k","Resistor_SMD:R_0603_1608Metric","2",""
"SV1","PROG (as old SV1)","field_eyes:MA03-2","1",""
"TH101","10k B3950 (under cell)","Resistor_SMD:R_0603_1608Metric","1",""
"TP301","STATUS","TestPoint:TestPoint_Pad_D1.5mm","1",""
"U101","CN3791","Package_SO:SSOP-10_3.9x4.9mm_P1.00mm","1",""
"U102","DW01A","Package_TO_SOT_SMD:SOT-23-6","1",""
"U103","XC6220B331MR","Package_TO_SOT_SMD:SOT-23-5","1",""
"U104","MT3608","Package_TO_SOT_SMD:SOT-23-6","1",""
"U201","ESP32-WROOM-32D","RF_Module:ESP32-WROOM-32D","1",""
"U301","A7672S","field_eyes:A7672S","1",""
"U302","SMF05C","Package_TO_SOT_SMD:SOT-363_SC-70-6","1",""
"U401,U402","MAX485ESA+T","Package_SO:SOIC-8_3.9x4.9mm_P1.27mm","2",""
"U403","MX1508","Package_SO:SOIC-16_3.9x9.9mm_P1.27mm","1",""
"U404","L78L09","Package_TO_SOT_SMD:SOT-89-3","1",""
"U405","L78L05","Package_TO_SOT_SMD:SOT-89-3","1",""
"X1","7-in-1 NPK (A B 12V GND)","field_eyes:JST_XH_04_LongPad","1",""
"X2","SMT100 (A B 12V GND)","field_eyes:JST_XH_04_LongPad","1",""
"X3","OLED (3V3 GND SDA SCL)","field_eyes:JST_XH_04_LongPad","1",""
"X4","DHT22 (NC 3V3 DATA GND)","field_eyes:JST_XH_04_LongPad","1",""
